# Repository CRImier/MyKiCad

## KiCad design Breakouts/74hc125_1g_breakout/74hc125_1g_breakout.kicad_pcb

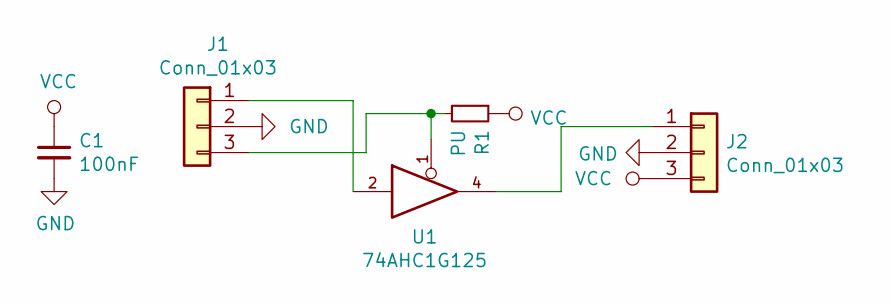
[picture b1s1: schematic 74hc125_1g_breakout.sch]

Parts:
C1: 100nF; C_0805_2012Metric_Pad1.15x1.40mm_HandSolder
J1, J2: Conn_01x03; PinHeader_1x03_P2.54mm_Vertical
R1: PU; R_0805_2012Metric_Pad1.15x1.40mm_HandSolder
U1: 74AHC1G125; SOT-353_SC-70-5_Handsoldering

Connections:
GND: C1.2, J1.2, J2.2, U1.3 (GND)
unnamed: J1.1, U1.2
unnamed: J1.3, R1.2, U1.1
unnamed: J2.1, U1.4
VCC: C1.1, J2.3, R1.1, U1.5 (VCC)

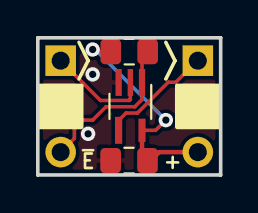
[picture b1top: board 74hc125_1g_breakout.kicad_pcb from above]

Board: 2 copper layers, 10.2 x 7.6 mm, 5 parts (0 on the bottom side), 5 nets.

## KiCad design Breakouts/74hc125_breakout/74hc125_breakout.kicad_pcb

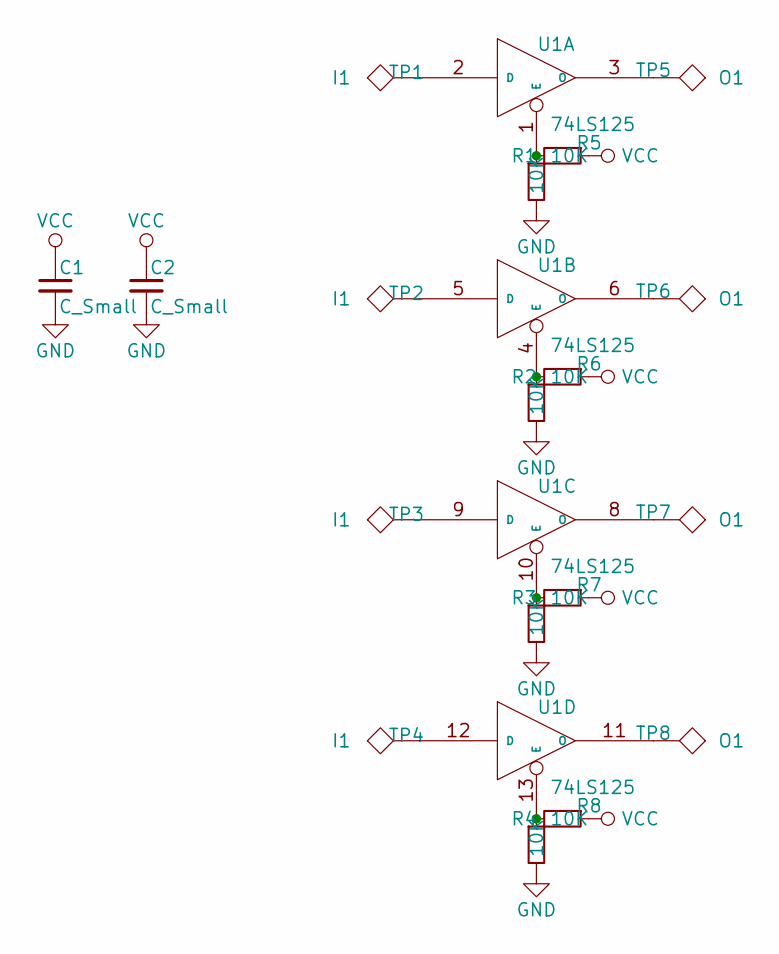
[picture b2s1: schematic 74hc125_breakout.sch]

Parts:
C1, C2: C_Small; C_0805_HandSoldering
R1, R2, R3, R4, R5, R6, R7, R8: 10K; R_0805_HandSoldering
TP1, TP2, TP3, TP4: I1; Measurement_Point_Round-SMD-Pad_Small
TP5, TP6, TP7, TP8: O1; Measurement_Point_Round-SMD-Pad_Small
U1: 74LS125; SOIC-14_3.9x8.7mm_Pitch1.27mm

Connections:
GND: C1.2, C2.2, R1.2, R2.2, R3.2, R4.2, U1.7 (GND)
unnamed: R1.1, R5.2, U1.1 (E)
unnamed: R2.1, R6.2, U1.4 (E)
unnamed: R3.1, R7.2, U1.10 (E)
unnamed: R4.1, R8.2, U1.13 (E)
unnamed: TP1.1, U1.2 (D)
unnamed: TP2.1, U1.5 (D)
unnamed: TP3.1, U1.9 (D)
unnamed: TP4.1, U1.12 (D)
unnamed: TP5.1, U1.3 (O)
unnamed: TP6.1, U1.6 (O)
unnamed: TP7.1, U1.8 (O)
unnamed: TP8.1, U1.11 (O)
VCC: C1.1, C2.1, R5.1, R6.1, R7.1, R8.1, U1.14 (VCC)

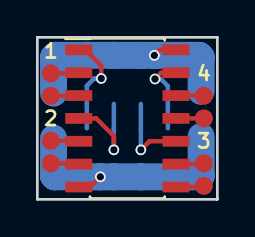
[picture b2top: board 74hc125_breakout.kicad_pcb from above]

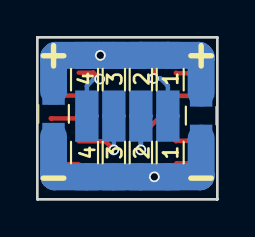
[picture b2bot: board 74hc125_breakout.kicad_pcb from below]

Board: 2 copper layers, 10.0 x 9.0 mm, 19 parts (10 on the bottom side), 14 nets.

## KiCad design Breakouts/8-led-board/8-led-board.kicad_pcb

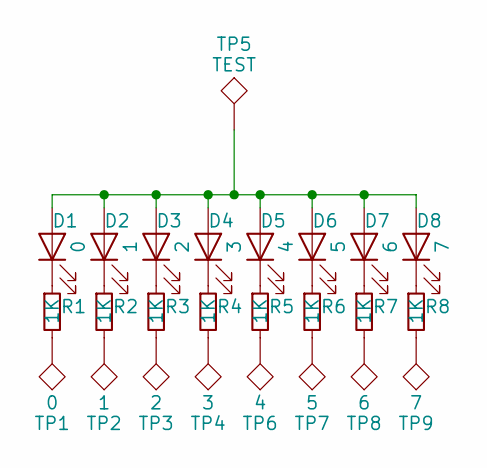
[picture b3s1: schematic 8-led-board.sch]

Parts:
D1: 0; LED_0805_HandSoldering
D2: 1; LED_0805_HandSoldering
D3: 2; LED_0805_HandSoldering
D4: 3; LED_0805_HandSoldering
D5: 4; LED_0805_HandSoldering
D6: 5; LED_0805_HandSoldering
D7: 6; LED_0805_HandSoldering
D8: 7; LED_0805_HandSoldering
R1, R2, R3, R4, R5, R6, R7, R8: 1K; R_0603_HandSoldering
TP1: 0; Measurement_Point_Round-SMD-Pad_Small
TP2: 1; Measurement_Point_Round-SMD-Pad_Small
TP3: 2; Measurement_Point_Round-SMD-Pad_Small
TP4: 3; Measurement_Point_Round-SMD-Pad_Small
TP5: TEST; Measurement_Point_Round-SMD-Pad_Big
TP6: 4; Measurement_Point_Round-SMD-Pad_Small
TP7: 5; Measurement_Point_Round-SMD-Pad_Small
TP8: 6; Measurement_Point_Round-SMD-Pad_Small
TP9: 7; Measurement_Point_Round-SMD-Pad_Small

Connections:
unnamed: D1.1 (K), R1.1
unnamed: D1.2 (A), D2.2 (A), D3.2 (A), D4.2 (A), D5.2 (A), D6.2 (A), D7.2 (A), D8.2 (A), TP5.1
unnamed: D2.1 (K), R2.1
unnamed: D3.1 (K), R3.1
unnamed: D4.1 (K), R4.1
unnamed: D5.1 (K), R5.1
unnamed: D6.1 (K), R6.1
unnamed: D7.1 (K), R7.1
unnamed: D8.1 (K), R8.1
unnamed: R1.2, TP1.1
unnamed: R2.2, TP2.1
unnamed: R3.2, TP3.1
unnamed: R4.2, TP4.1
unnamed: R5.2, TP6.1
unnamed: R6.2, TP7.1
unnamed: R7.2, TP8.1
unnamed: R8.2, TP9.1

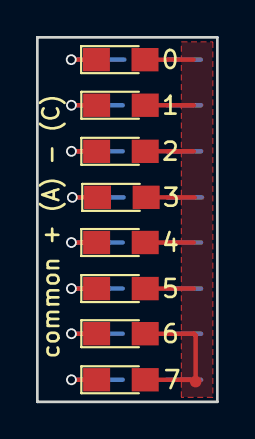
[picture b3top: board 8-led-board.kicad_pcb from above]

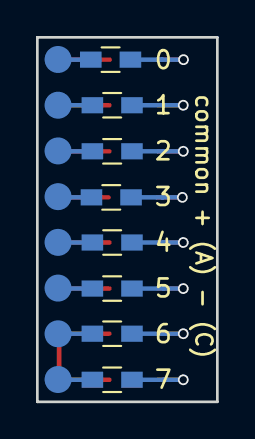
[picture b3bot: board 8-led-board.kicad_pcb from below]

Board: 2 copper layers, 10.0 x 20.2 mm, 25 parts (16 on the bottom side), 17 nets.

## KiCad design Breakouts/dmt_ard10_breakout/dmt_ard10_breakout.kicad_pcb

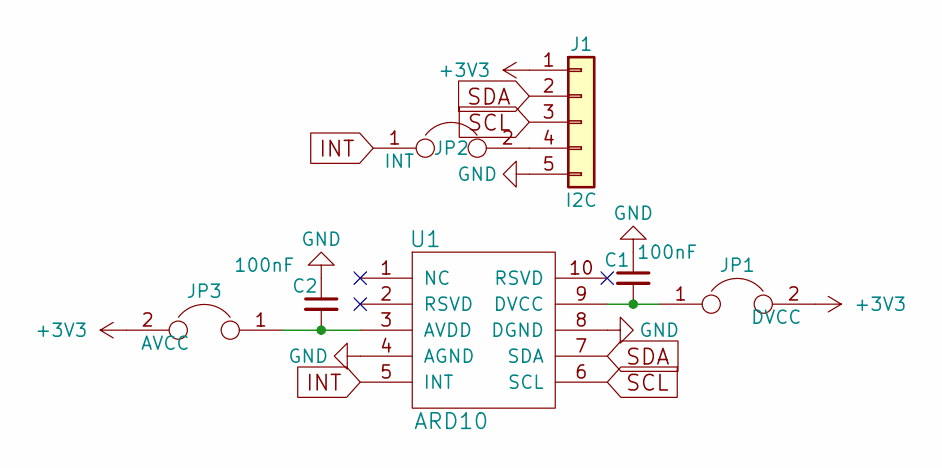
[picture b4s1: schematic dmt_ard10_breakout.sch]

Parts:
C1, C2: 100nF; C_0805
J1: I2C; Pin_Header_Straight_1x05_Pitch2.54mm
JP1: DVCC; GS2_SMALL
JP2: INT; GS2_SMALL
JP3: AVCC; GS2_SMALL
U1: ARD10; DFN-10_3x3mm_Pitch0.5mm

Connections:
+3V3: J1.1, JP1.2, JP3.2
GND: C1.1, C2.1, J1.5, U1.4 (AGND), U1.8 (DGND)
INT: JP2.1, U1.5 (INT)
unnamed: C1.2, JP1.1, U1.9 (DVCC)
unnamed: C2.2, JP3.1, U1.3 (AVDD)
unnamed: J1.4, JP2.2
SCL: J1.3, U1.6 (SCL)
SDA: J1.2, U1.7 (SDA)

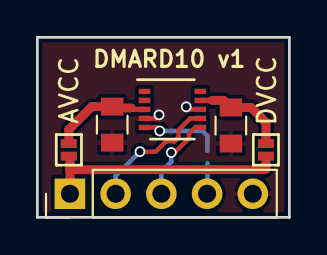
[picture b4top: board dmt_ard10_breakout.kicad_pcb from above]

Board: 2 copper layers, 14.0 x 10.0 mm, 7 parts (1 on the bottom side), 8 nets.

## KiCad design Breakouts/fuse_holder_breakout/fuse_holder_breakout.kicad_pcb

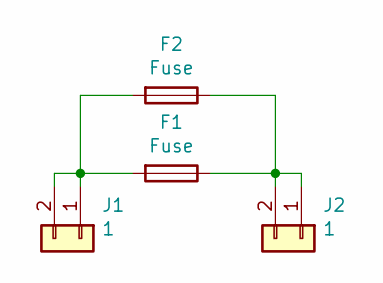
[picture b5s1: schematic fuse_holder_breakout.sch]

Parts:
F1: Fuse; Fuseholder5x20_horiz_open_universal_Type-III
F2: Fuse; Fuseholder5x20_horiz_SemiClosed_Casing10x25mm
J1, J2: 1; WireConnection_2mmDrill

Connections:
unnamed: F1.1, F2.1, J2.1, J2.2
unnamed: F1.2, F2.2, J1.1, J1.2

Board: 2 copper layers, 4 parts (0 on the bottom side), 2 nets, no tracks yet.

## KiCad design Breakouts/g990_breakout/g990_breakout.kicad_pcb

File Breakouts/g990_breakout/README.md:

# G990 breakout 

This is the breakout for a G990 linear fan controller IC. Is an old IC. I have 10pcs of that IC, so I'm building this breakout.

Board says "G990 fan ctrl brkt by Arya".

Schematic mostly borrowed from Lenovo X100E laptop schematic.

## Notes

- Pin headers are arranged in a way that this board can be plugged into a breadboard.
- Signal names are silkscreened on the board's bottom layer.
- This board is untested and there's no guarantees of fitness.

## Info

- Software: Kicad 6
- Version: 1
- PCB size: 16x14mm
- Layer count: 2

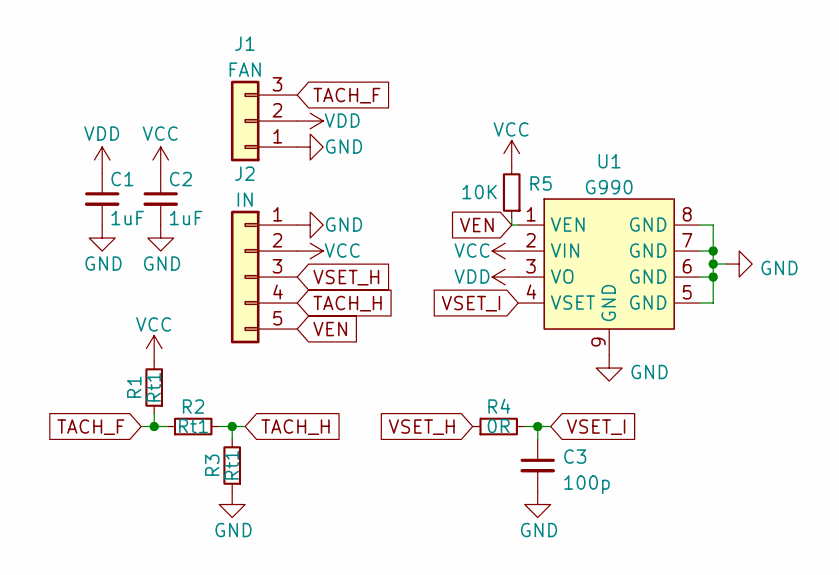
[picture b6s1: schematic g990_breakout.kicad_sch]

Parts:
C1, C2: 1uF; C_0603_1608Metric
C3: 100p; C_0603_1608Metric
J1: FAN; PinHeader_1x03_P2.54mm_Vertical
J2: IN; PinHeader_1x05_P2.54mm_Vertical
R1, R2, R3: Rt1; R_0603_1608Metric
R4: 0R; R_0603_1608Metric
R5: 10K; R_0603_1608Metric
U1: G990; SOIC-8-1EP_3.9x4.9mm_P1.27mm_EP2.29x3mm

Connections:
GND: C1.2, C2.2, C3.2, J1.1, J2.1, R3.1, U1.5 (GND), U1.6 (GND), U1.7 (GND), U1.8 (GND), U1.9 (GND)
TACH_F: J1.3, R1.1, R2.1
TACH_H: J2.4, R2.2, R3.2
VCC: C2.1, J2.2, R1.2, R5.2, U1.2 (VIN)
VDD: C1.1, J1.2, U1.3 (VO)
VEN: J2.5, R5.1, U1.1 (VEN)
VSET_H: J2.3, R4.1
VSET_I: C3.1, R4.2, U1.4 (VSET)

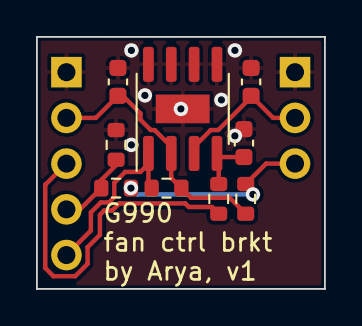
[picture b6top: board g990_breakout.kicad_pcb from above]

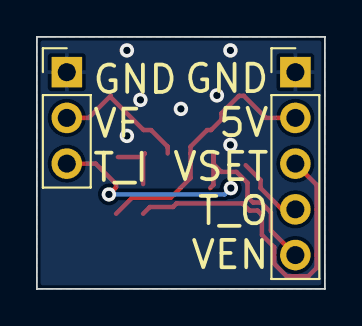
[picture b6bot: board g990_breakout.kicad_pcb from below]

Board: 2 copper layers, 16.0 x 14.0 mm, 11 parts (2 on the bottom side), 8 nets.

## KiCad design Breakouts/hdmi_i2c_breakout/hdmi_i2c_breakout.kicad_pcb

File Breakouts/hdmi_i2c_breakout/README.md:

# Video I2C helper

This is a helper board that allows you to connect I2C devices through your laptop's/SBC's video output port.
It provides a way to attach a three-row straight/angled pin header. It also exposes HPD, CEC and UTIL pins on a separate pin header.
It provides optional SDA&SCL level shifting down to 3.3V and a linear regulator to 3.3V.
It also provides a QWIIC/StemmaQT connector (VSW-connected) and an LED that lights up when VSW is set to 5V.
I2C pinout is heavily influenced by the Raspberry Pi pinout, and the board exposes +5V, GND and +3.3V on extra pin header connections.

## Changes in v2:

- Switched to KiCad 6
- Fixed issue where +VSW and +5V were swapped places, causing SDA to be pulled up to +5V no matter the output voltage
- Added a QWIIC/StemmaQT connector
- Added an LED to signal 5V mode
- Removed paste from HDMI connector pads
- Removed some weird mask pads from the HDMI connector shield pins
- Re-drew silkscreen a bit

- Signal names are silkscreened on the board's bottom layer.
- This repository also includes files for manufacturing a 3x5 panel.

- Version: 2
- Software: Kicad 5
- PCB size: 30.1*20.8mm
- Layer count: 2
- Recommended thickness: 1.6mm (HDMI side plug fits well on 1.6mm boards)

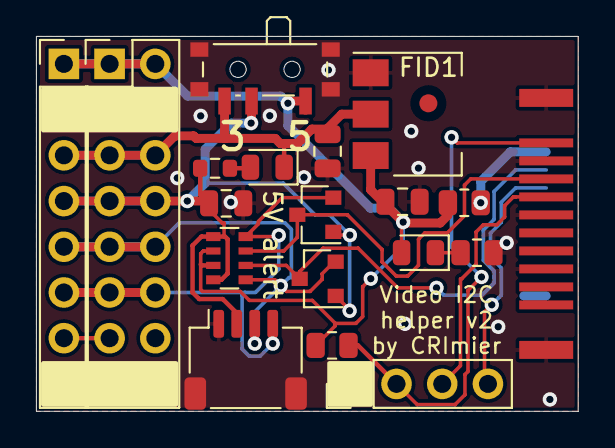
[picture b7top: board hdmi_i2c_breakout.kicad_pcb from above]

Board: 2 copper layers, 30.1 x 20.8 mm, 20 parts (0 on the bottom side), 14 nets.

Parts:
C1, C2, C3: 100nF; C_0805_2012Metric
D1: LED_Small; D_0805_2012Metric
D2: 5V_ALRT; D_0805_2012Metric
FID1: Fiducial; Fiducial_1mm_Mask2mm
J1: ROW1; PinHeader_1x08_P2.54mm_Vertical
J2: ROW23; PinHeader_2x08_P2.54mm_Vertical
J3: AUX; PinHeader_1x04_P2.54mm_Vertical
J4: HDMI_A; HDMI_PLUG_SIDE
J5: QWIIC; JST_SH_SM04B-SRSS-TB_1x04-1MP_P1.00mm_Horizontal
Q1, Q2: Q_NMOS_GSD; SOT-23
R1: 1K; R_0805_2012Metric
R2: 0R; R_0805_2012Metric
R3: 10K; R_0805_2012Metric
R4: 120R; R_0603_1608Metric
RN1: 10K; R_Array_Convex_4x0603
SW1: SW_SPDT; SW_SPDT_PCM12
U1: AP1117-33; SOT-223-3_TabPin2

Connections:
+3V3: C1.1, D2.1 (K), J1.3, J2.5, J2.6, SW1.3 (C), U1.2 (VO)
+5V: C2.1, D1.2 (A), J1.1, J2.1, J2.2, R1.1, R2.2, RN1.2 (R2.1), RN1.3 (R3.1), SW1.1 (A), U1.3 (VI)
+VSW: C3.1, J1.4, J2.7, J2.8, J5.2, Q1.1 (G), Q2.1 (G), R4.1, RN1.1 (R1.1), RN1.4 (R4.1), SW1.2 (B)
CEC: J3.3, J4.13 (CEC)
GND: C1.2, C2.2, C3.2, J1.2, J1.8, J2.3, J2.4, J2.15, J2.16, J3.1, J4.2 (D2S), J4.5 (D1S), J4.8 (D0S), J4.11 (CKS), J4.17 (GND), J4.SH, J5.1, J5.MP (MountPin), R3.2, SW1.SH, U1.1 (GND)
HPD: J3.2, J4.19 (HPD), R1.2
unnamed: D1.1 (K), R3.1
unnamed: D2.2 (A), R4.2
unnamed: J4.18 (+5V), R2.1
SCL_5V: J4.15 (SCL), Q1.3 (D), RN1.7 (R2.2)
SCL_SW: J1.6, J2.11, J2.12, J5.4, Q1.2 (S), RN1.8 (R1.2)
SDA_5V: J4.16 (SDA), Q2.3 (D), RN1.6 (R3.2)
SDA_SW: J1.5, J2.9, J2.10, J5.3, Q2.2 (S), RN1.5 (R4.2)
UTIL: J3.4, J4.14 (UTILITY)

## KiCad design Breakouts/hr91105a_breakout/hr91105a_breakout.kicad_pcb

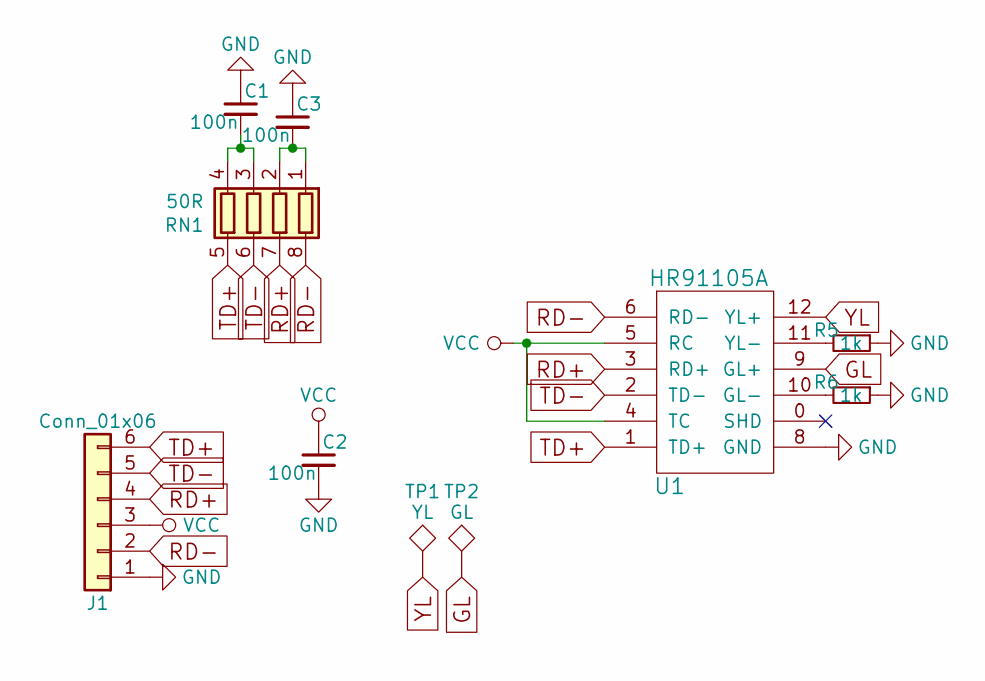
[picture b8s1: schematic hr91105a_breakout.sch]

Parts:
C1, C2, C3: 100n; C_0603
J1: Conn_01x06; Pin_Header_Straight_1x06_Pitch2.54mm
R5, R6: 1k; R_0603
RN1: 50R; R_Array_Concave_4x0603
TP1: YL; Measurement_Point_Round-TH_Small
TP2: GL; Measurement_Point_Round-TH_Small
U1: HR91105A; HR911105_RJ45

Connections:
GL: TP2.1, U1.9 (GL+)
GND: C1.1, C2.2, C3.1, J1.1, R5.1, R6.1, U1.0 (SHD), U1.8 (GND)
unnamed: C1.2, RN1.3 (R3.1), RN1.4 (R4.1)
unnamed: C3.2, RN1.1 (R1.1), RN1.2 (R2.1)
unnamed: R5.2, U1.11 (YL-)
unnamed: R6.2, U1.10 (GL-)
RD+: J1.4, RN1.7 (R2.2), U1.3 (RD+)
RD-: J1.2, RN1.8 (R1.2), U1.6 (RD-)
TD+: J1.6, RN1.5 (R4.2), U1.1 (TD+)
TD-: J1.5, RN1.6 (R3.2), U1.2 (TD-)
VCC: C2.1, J1.3, U1.4 (TC), U1.5 (RC)
YL: TP1.1, U1.12 (YL+)

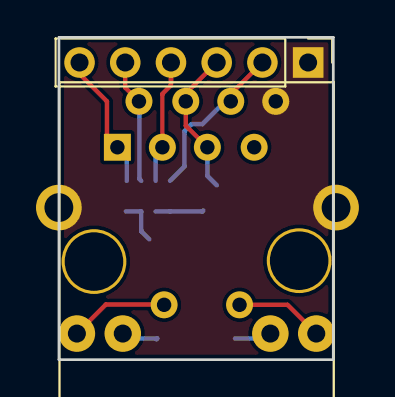
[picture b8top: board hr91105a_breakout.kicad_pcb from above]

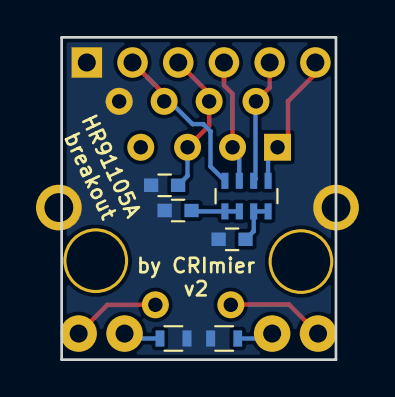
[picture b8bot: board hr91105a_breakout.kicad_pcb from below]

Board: 2 copper layers, 15.2 x 17.9 mm, 10 parts (6 on the bottom side), 12 nets.
